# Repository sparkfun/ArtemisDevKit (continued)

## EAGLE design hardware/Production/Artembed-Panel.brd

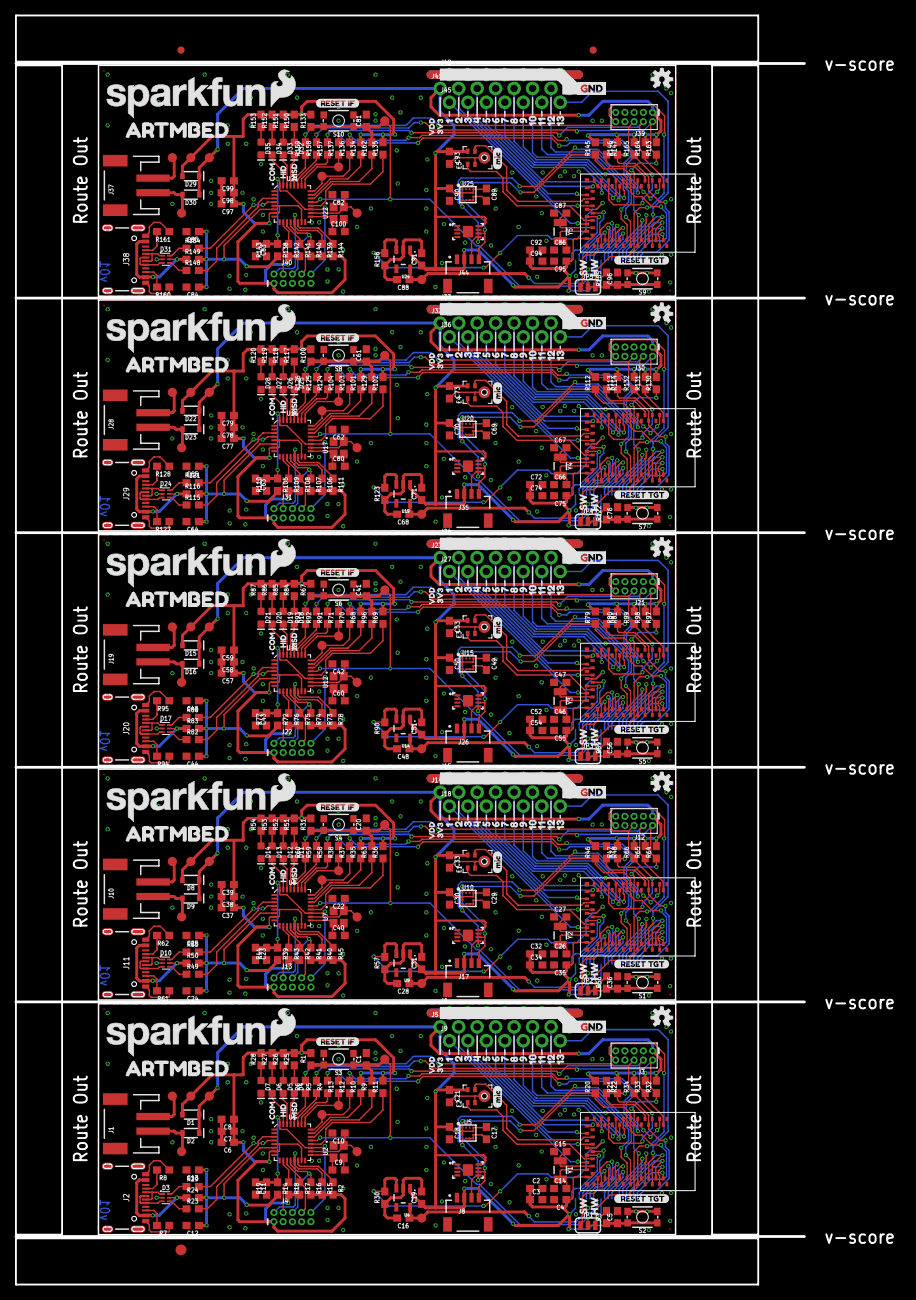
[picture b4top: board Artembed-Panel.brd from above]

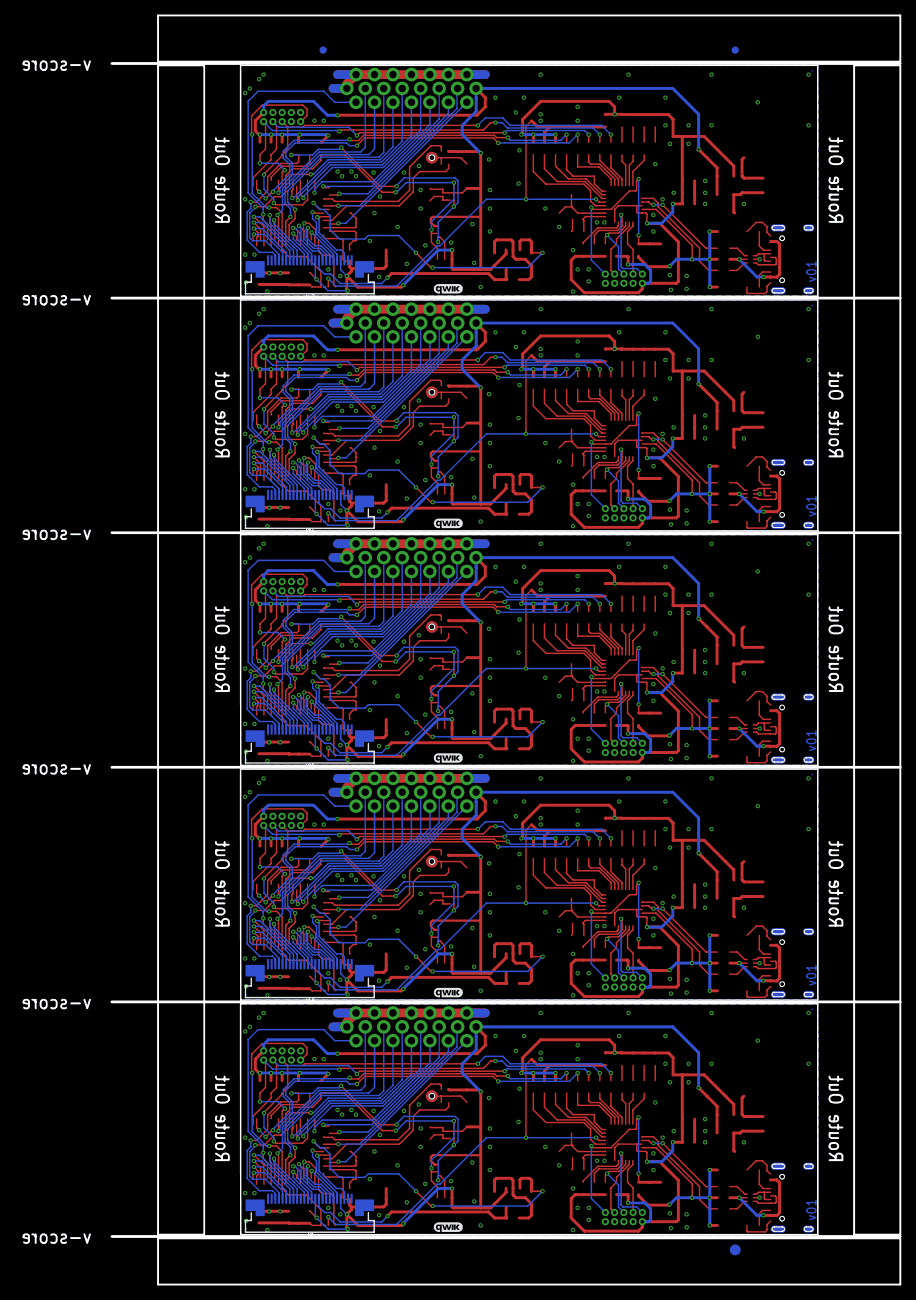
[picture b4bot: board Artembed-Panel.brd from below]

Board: 2 copper layers, 108.4 x 174.5 mm, 616 parts (23 on the bottom side), 405 nets.

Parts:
C1, C4, C7, C8, C11, C13, C17, C20, C23, C25, C29, C35, C38, C39, C41, C43, C45, C49, C55, C58, C59, C61, C63, C65, C69, C75, C78, C79, C81, C83, C85, C89, C95, C98, C99: 0.1uF; 0603
C2, C18, C30, C32, C50, C52, C70, C72, C90, C92: 10uF; 0603
C3, C12, C16, C19, C21, C24, C28, C31, C33, C34, C44, C48, C51, C53, C54, C64, C68, C71, C73, C74, C84, C88, C91, C93, C94: 1.0uF; 0603
C5, C36, C56, C76, C96: 1nF; 0603
C6, C37, C57, C77, C97: 2.2uF; 0603
C9, C10, C22, C40, C42, C60, C62, C80, C82, C100: 12pF; 0603
C14, C15, C26, C27, C46, C47, C66, C67, C86, C87: 15pF; 0603
D1, D2, D8, D9, D15, D16, D22, D23, D29, D30: 3A/10V/280mV; SOD-323
D3, D10, D17, D24, D31: PRTR5V0U2F; SOT886
D4, D11, D18, D25, D32: BLUE; LED-0603
D5, D12, D19, D26, D33: GREEN; LED-0603
D6, D13, D20, D27, D34: Yellow; LED-0603
D7, D14, D21, D28, D35: RED; LED-0603
E1, E2, E3, E4, E5: SPH0641LM4H-1; SPH0641LM4H-1_MICROPHONE
E$1, E$2, E$3, E$4: FIDUCIAL-1X2
E$5, E$6: FIDUCIAL-1.5X3
ECC1, ECC2, ECC3, ECC4, ECC5: ATECC508AUDFN_2X3MM; UDFN_2X3MM
FD1, FD2, FD3, FD4, FD5, FD6, FD7, FD8, FD9, FD10, FD11, FD12, FD13, FD14, FD15, FD16, FD17, FD18, FD19, FD20: FIDUCIAL0.2MM; FIDUCIAL-0.2MM
J1, J10, J19, J28, J37: JST-2-SMD
J2, J11, J20, J29, J38: USB-C-16P
J3, J12, J21, J30, J39: CORTEX_JTAG_DEBUG_MINIMUM_PTH; 2X5-PTH-1.27MM
J4, J13, J22, J31, J40: CORTEX_JTAG_DEBUG_PTH_NS; 2X5-PTH-1.27MM-NO_SILK
J5, J14, J23, J32, J41: 1X08_NO_SILK
J6, J9, J15, J18, J24, J27, J33, J36, J42, J45: 1X07_NO_SILK
J7, J16, J25, J34, J43: CAMERA-HIMAX; FPC-24-AMPHENOL-SFV24R-1STE1HLF
J8, J17, J26, J35, J44: JST04_1MM_RA
JP1, JP2, JP3, JP4, JP5: HW/SW RESET; SMT-JUMPER_3_1-NC_TRACE_SILK
LOGO1, LOGO3, LOGO5, LOGO7, LOGO9: OSHW-LOGOS; OSHW-LOGO-S
LOGO2, LOGO4, LOGO6, LOGO8, LOGO10: SFE_LOGO_NAME.2_INCH; SFE_LOGO_NAME_.2
R1, R2, R3, R19, R22, R30, R31, R44, R45, R48, R56, R57, R67, R77, R78, R81, R89, R90, R100, R110, R111, R114, R122, R123, R133, R143, R144, R147, R155, R156: 10k; 0603
R4, R5, R6, R9, R12, R13, R37, R38, R58, R59, R60, R63, R70, R71, R91, R92, R93, R96, R103, R104, R124, R125, R126, R129, R136, R137, R157, R158, R159, R162: 0; 0603
R7, R8, R61, R62, R94, R95, R127, R128, R160, R161: 5.1k; 0603
R10, R11, R15, R16, R17, R18, R32, R33, R34, R35, R36, R40, R41, R42, R43, R64, R65, R66, R68, R69, R73, R74, R75, R76, R97, R98, R99, R101, R102, R106, R107, R108, R109, R130, R131, R132, R134, R135, R139, R140, R141, R142, R163, R164, R165: DNP; 0603
R14, R39, R72, R105, R138: 5.62k; 0603
R20, R21, R46, R47, R79, R80, R112, R113, R145, R146: 2.2k; 0603
R23, R29, R49, R55, R82, R88, R115, R121, R148, R154: 33; 0603
R24, R50, R83, R116, R149: 10; 0603
R25, R26, R27, R28, R51, R52, R53, R54, R84, R85, R86, R87, R117, R118, R119, R120, R150, R151, R152, R153: 330; 0603
S1, S2, S5, S7, S9: RESET TGT; TACTILE_SWITCH_SMD_4.6X2.8MM
S3, S4, S6, S8, S10: RESET IF; TACTILE_SWITCH_SMD_4.6X2.8MM
TP1, TP2, TP19, TP28, TP37: TEST-POINT3X5; PAD.03X.05
TP3, TP4, TP5, TP6, TP7, TP8, TP9, TP10, TP11, TP12, TP13, TP14, TP15, TP16, TP17, TP18, TP20, TP21, TP22, TP23, TP24, TP25, TP26, TP27, TP29, TP30, TP31, TP32, TP33, TP34, TP35, TP36, TP38, TP39, TP40, TP41, TP42, TP43, TP44, TP45: PAD.03X.05
U1, U6, U11, U16, U21: DAPLINK_KL26Z; QFN-32-NOPAD
U2, U7, U12, U17, U22: 16MHz; CRYSTAL-SMD-2X2.5MM
U3, U8, U13, U18, U23: ARTEMIS_MODULESMD; ARTEMIS_FP
U4, U9, U14, U19, U24: 1.8V; SOT23-5
U5, U10, U15, U20, U25: LIS2DH12; LGA-12-LISDH12
U$1, U$15, U$55, U$82, U$109: 10
U$2, U$29, U$56, U$83, U$110: 21
U$3, U$30, U$57, U$84, U$111: 32
U$4, U$31, U$58, U$85, U$112: 43
U$5, U$32, U$59, U$86, U$113: 54
U$6, U$33, U$60, U$87, U$114: 65
U$7, U$34, U$61, U$88, U$115: 76
U$8, U$35, U$62, U$89, U$116: 87
U$9, U$36, U$63, U$90, U$117: 98
U$10, U$37, U$64, U$91, U$118: 109
U$11, U$38, U$65, U$92, U$119: 1110
U$12, U$39, U$66, U$93, U$120: 1211
U$13, U$40, U$67, U$94, U$121: 1312
U$14, U$41, U$68, U$95, U$122: GND13
U$16, U$42, U$69, U$96, U$123: SFE_LOGO_FLAME_.2
U$17, U$43, U$70, U$97, U$124: ARTMBED17
U$18, U$44, U$71, U$98, U$125: QWIIC_4MM
U$19, U$45, U$72, U$99, U$126: COM7
U$20, U$46, U$73, U$100, U$127: HID5
U$21, U$47, U$74, U$101, U$128: MSD6
U$22, U$48, U$75, U$102, U$129: MIC0
U$23, U$49, U$76, U$103, U$130: HW3
U$24, U$50, U$77, U$104, U$131: SW4
U$25, U$51, U$78, U$105, U$132: _RESET_TGT2
U$26, U$52, U$79, U$106, U$133: RESET_IF1
U$27, U$53, U$80, U$107, U$134: 3V39
U$28, U$54, U$81, U$108, U$135: VDD8
Y1, Y2, Y3, Y4, Y5: 32.768kHz; CRYSTAL-SMD-3.2X1.5MM

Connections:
1.8V: C16.1, J7.10, TP1.P$1, U4.5
1.8V1: C28.1, J16.10, TP2.P$1, U9.5
1.8V2: C48.1, J25.10, TP19.P$1, U14.5
1.8V3: C68.1, J34.10, TP28.P$1, U19.5
1.8V4: C88.1, J43.10, TP37.P$1, U24.5
3.3V: C6.1, C7.1, C8.1, D1.A, J4.1, R1.2, R2.2, R10.2, R11.2, R15.2, R16.2, R17.2, R18.2, R25.2, R26.2, R27.2, R28.2, TP13.P$1, U1.5, U1.7, U1.15
3.3V1: C37.1, C38.1, C39.1, D8.A, J13.1, R31.2, R35.2, R36.2, R40.2, R41.2, R42.2, R43.2, R45.2, R51.2, R52.2, R53.2, R54.2, TP14.P$1, U6.5, U6.7, U6.15
3.3V2: C57.1, C58.1, C59.1, D15.A, J22.1, R67.2, R68.2, R69.2, R73.2, R74.2, R75.2, R76.2, R78.2, R84.2, R85.2, R86.2, R87.2, TP23.P$1, U11.5, U11.7, U11.15
3.3V3: C77.1, C78.1, C79.1, D22.A, J31.1, R100.2, R101.2, R102.2, R106.2, R107.2, R108.2, R109.2, R111.2, R117.2, R118.2, R119.2, R120.2, TP32.P$1, U16.5, U16.7, U16.15
3.3V4: C97.1, C98.1, C99.1, D29.A, J40.1, R133.2, R134.2, R135.2, R139.2, R140.2, R141.2, R142.2, R144.2, R150.2, R151.2, R152.2, R153.2, TP41.P$1, U21.5, U21.7, U21.15
!RST: C11.1, J4.10, R14.1, R19.2, U1.19, U1.32
!RST1: C23.1, J13.10, R39.1, R44.2, U6.19, U6.32
!RST2: C43.1, J22.10, R72.1, R77.2, U11.19, U11.32
!RST3: C63.1, J31.10, R105.1, R110.2, U16.19, U16.32
!RST4: C83.1, J40.10, R138.1, R143.2, U21.19, U21.32
!TGT_RST: C1.1, JP1.2, R1.1, R9.2, S3.3, S3.4, TP11.P$1, U1.21
!TGT_RST1: C20.1, JP2.2, R31.1, R63.2, S4.3, S4.4, TP7.P$1, U6.21
!TGT_RST2: C41.1, JP3.2, R67.1, R96.2, S6.3, S6.4, TP21.P$1, U11.21
!TGT_RST3: C61.1, JP4.2, R100.1, R129.2, S8.3, S8.4, TP30.P$1, U16.21
!TGT_RST4: C81.1, JP5.2, R133.1, R162.2, S10.3, S10.4, TP39.P$1, U21.21
!TGT_RST!_HW: C5.1, J3.10, JP1.3, R3.1, S2.3, S2.4, U3.~RST
!TGT_RST!_HW1: C36.1, J12.10, JP2.3, R56.1, S1.3, S1.4, U8.~RST
!TGT_RST!_HW2: C56.1, J21.10, JP3.3, R89.1, S5.3, S5.4, U13.~RST
!TGT_RST!_HW3: C76.1, J30.10, JP4.3, R122.1, S7.3, S7.4, U18.~RST
!TGT_RST!_HW4: C96.1, J39.10, JP5.3, R155.1, S9.3, S9.4, U23.~RST
!TGT_RST!_SW: JP1.1, U3.~D19
!TGT_RST!_SW1: JP2.1, U8.~D19
!TGT_RST!_SW2: JP3.1, U13.~D19
!TGT_RST!_SW3: JP4.1, U18.~D19
!TGT_RST!_SW4: JP5.1, U23.~D19
CAMERA_D0: J7.14, U3.~D43
CAMERA_D1: J7.3, U3.AD34
CAMERA_D2: J7.9, U3.~AD31
CAMERA_D3: J7.5, U3.~AD33/SWO
CAMERA_D4: J7.12, U3.D41
CAMERA_D5: J7.20, U3.~D44
CAMERA_D6: J7.19, U3.~D37
CAMERA_D7: J7.13, U3.~D45
CAMERA_D8: J16.3, U8.AD34
CAMERA_D9: J16.5, U8.~AD33/SWO
CAMERA_D10: J16.12, U8.D41
CAMERA_D11: J16.20, U8.~D44
CAMERA_D12: J16.19, U8.~D37
CAMERA_D13: J16.13, U8.~D45
CAMERA_D14: J16.14, U8.~D43
CAMERA_D15: J16.9, U8.~AD31
CAMERA_D16: J25.3, U13.AD34
CAMERA_D17: J25.5, U13.~AD33/SWO
CAMERA_D18: J25.12, U13.D41
CAMERA_D19: J25.20, U13.~D44
CAMERA_D20: J25.19, U13.~D37
CAMERA_D21: J25.13, U13.~D45
CAMERA_D22: J25.14, U13.~D43
CAMERA_D23: J25.9, U13.~AD31
CAMERA_D24: J34.3, U18.AD34
CAMERA_D25: J34.5, U18.~AD33/SWO
CAMERA_D26: J34.12, U18.D41
CAMERA_D27: J34.20, U18.~D44
CAMERA_D28: J34.19, U18.~D37
CAMERA_D29: J34.13, U18.~D45
CAMERA_D30: J34.14, U18.~D43
CAMERA_D31: J34.9, U18.~AD31
CAMERA_D32: J43.3, U23.AD34
CAMERA_D33: J43.5, U23.~AD33/SWO
CAMERA_D34: J43.12, U23.D41
CAMERA_D35: J43.20, U23.~D44
CAMERA_D36: J43.19, U23.~D37
CAMERA_D37: J43.13, U23.~D45
CAMERA_D38: J43.14, U23.~D43
CAMERA_D39: J43.9, U23.~AD31
CAMERA_DVDD_EN: R30.2, U3.D15, U4.3
CAMERA_DVDD_EN1: R57.2, U8.D15, U9.3
CAMERA_DVDD_EN2: R90.2, U13.D15, U14.3
CAMERA_DVDD_EN3: R123.2, U18.D15, U19.3
CAMERA_DVDD_EN4: R156.2, U23.D15, U24.3
CAMERA_HSYNC: J7.16, U3.~D42
CAMERA_HSYNC1: J16.16, U8.~D42
CAMERA_HSYNC2: J25.16, U13.~D42
CAMERA_HSYNC3: J34.16, U18.~D42
CAMERA_HSYNC4: J43.16, U23.~D42
CAMERA_INT: J7.18, U3.D38
CAMERA_INT1: J16.18, U8.D38
CAMERA_INT2: J25.18, U13.D38
CAMERA_INT3: J34.18, U18.D38
CAMERA_INT4: J43.18, U23.D38
CAMERA_MCLK: J7.8, U3.~D18
CAMERA_MCLK1: J16.8, U8.~D18
CAMERA_MCLK2: J25.8, U13.~D18
CAMERA_MCLK3: J34.8, U18.~D18
CAMERA_MCLK4: J43.8, U23.~D18
CAMERA_PCLK: J7.17, U3.D36
CAMERA_PCLK1: J16.17, U8.D36
CAMERA_PCLK2: J25.17, U13.D36
CAMERA_PCLK3: J34.17, U18.D36
CAMERA_PCLK4: J43.17, U23.D36
CAMERA_TRIG: J7.7, U3.D17
CAMERA_TRIG1: J16.7, U8.D17
CAMERA_TRIG2: J25.7, U13.D17
CAMERA_TRIG3: J34.7, U18.D17
CAMERA_TRIG4: J43.7, U23.D17
CAMERA_VSYNC: J7.6, U3.AD16
CAMERA_VSYNC1: J16.6, U8.AD16
CAMERA_VSYNC2: J25.6, U13.AD16
CAMERA_VSYNC3: J34.6, U18.AD16
CAMERA_VSYNC4: J43.6, U23.AD16
D1: J9.1, U3.~AD29
D2: J5.2, U3.~AD13
D3: J9.2, U3.~D25
D4: J5.3, U3.~D6
D5: J9.3, U3.~D27
D6: J5.4, U3.~D4
D7: J9.4, U3.~AD35
D8: J5.5, U3.D7
D9: J9.5, U3.~D5
D10: J5.6, U3.D2
D11: J9.6, U3.D1
D12: J5.7, U3.D0
D13: J9.7, U3.D3
D14: J18.7, U8.D3
D15: J18.1, U8.~AD29
D16: J14.2, U8.~AD13
D17: J18.2, U8.~D25
D18: J14.3, U8.~D6
D19: J18.3, U8.~D27
D20: J14.4, U8.~D4
D21: J18.4, U8.~AD35
D22: J14.5, U8.D7
D23: J18.5, U8.~D5
D24: J14.6, U8.D2
D25: J18.6, U8.D1
D26: J14.7, U8.D0
D27: J27.7, U13.D3
D28: J27.1, U13.~AD29
D29: J23.2, U13.~AD13
D30: J27.2, U13.~D25
D31: J23.3, U13.~D6
D32: J27.3, U13.~D27
D33: J23.4, U13.~D4
D34: J27.4, U13.~AD35
D35: J23.5, U13.D7
D36: J27.5, U13.~D5
D37: J23.6, U13.D2
D38: J27.6, U13.D1
D39: J23.7, U13.D0
D40: J36.7, U18.D3
D41: J36.1, U18.~AD29
D42: J32.2, U18.~AD13
D43: J36.2, U18.~D25
D44: J32.3, U18.~D6
D45: J36.3, U18.~D27
D46: J32.4, U18.~D4
D47: J36.4, U18.~AD35
D48: J32.5, U18.D7
D49: J36.5, U18.~D5
D50: J32.6, U18.D2
D51: J36.6, U18.D1
D52: J32.7, U18.D0
D53: J45.7, U23.D3
D54: J45.1, U23.~AD29
D55: J41.2, U23.~AD13
D56: J45.2, U23.~D25
D57: J41.3, U23.~D6
D58: J45.3, U23.~D27
D59: J41.4, U23.~D4
D60: J45.4, U23.~AD35
D61: J41.5, U23.D7
D62: J45.5, U23.~D5
D63: J41.6, U23.D2
D64: J45.6, U23.D1
D65: J41.7, U23.D0
GND: C1.2, C2.2, C3.2, C4.2, C5.2, C6.2, C7.2, C8.2, C9.2, C10.2, C11.2, C12.2, C13.2, C14.1, C15.1, C16.2, C17.2, C18.2, C19.2, C21.2, D3.2, D7.C, E2.2, E2.3, E2.6, E2.7, E2.8, ECC1.4, ECC1.P, J1.2, J2.GND, J2.GND2, J3.3, J3.5, J3.9, J4.3, J4.5, J4.9, J5.8, J6.1, J6.2, J6.3, J6.4, J6.5, J6.6, J6.7, J7.2, J7.15, J8.1, R7.1, R8.1, R19.1, R22.1, R30.1, S2.1, S2.2, S3.1, S3.2, TP9.P$1, U1.2, U1.8, U1.16, U2.P2, U2.P4, U3.GND@1, U3.GND@22, U3.GND@38, U3.GND@39, U3.GND@47, U3.GND@59, U4.2, U5.5, U5.6, U5.7, U5.8
GND1: C20.2, C22.2, C23.2, C24.2, C25.2, C26.1, C27.1, C28.2, C29.2, C30.2, C31.2, C32.2, C33.2, C34.2, C35.2, C36.2, C37.2, C38.2, C39.2, C40.2, D10.2, D14.C, E1.2, E1.3, E1.6, E1.7, E1.8, ECC2.4, ECC2.P, J10.2, J11.GND, J11.GND2, J12.3, J12.5, J12.9, J13.3, J13.5, J13.9, J14.8, J15.1, J15.2, J15.3, J15.4, J15.5, J15.6, J15.7, J16.2, J16.15, J17.1, R44.1, R48.1, R57.1, R61.1, R62.1, S1.1, S1.2, S4.1, S4.2, TP18.P$1, U6.2, U6.8, U6.16, U7.P2, U7.P4, U8.GND@1, U8.GND@22, U8.GND@38, U8.GND@39, U8.GND@47, U8.GND@59, U9.2, U10.5, U10.6, U10.7, U10.8
GND2: C41.2, C42.2, C43.2, C44.2, C45.2, C46.1, C47.1, C48.2, C49.2, C50.2, C51.2, C52.2, C53.2, C54.2, C55.2, C56.2, C57.2, C58.2, C59.2, C60.2, D17.2, D21.C, E3.2, E3.3, E3.6, E3.7, E3.8, ECC3.4, ECC3.P, J19.2, J20.GND, J20.GND2, J21.3, J21.5, J21.9, J22.3, J22.5, J22.9, J23.8, J24.1, J24.2, J24.3, J24.4, J24.5, J24.6, J24.7, J25.2, J25.15, J26.1, R77.1, R81.1, R90.1, R94.1, R95.1, S5.1, S5.2, S6.1, S6.2, TP27.P$1, U11.2, U11.8, U11.16, U12.P2, U12.P4, U13.GND@1, U13.GND@22, U13.GND@38, U13.GND@39, U13.GND@47, U13.GND@59, U14.2, U15.5, U15.6, U15.7, U15.8
GND3: C61.2, C62.2, C63.2, C64.2, C65.2, C66.1, C67.1, C68.2, C69.2, C70.2, C71.2, C72.2, C73.2, C74.2, C75.2, C76.2, C77.2, C78.2, C79.2, C80.2, D24.2, D28.C, E4.2, E4.3, E4.6, E4.7, E4.8, ECC4.4, ECC4.P, J28.2, J29.GND, J29.GND2, J30.3, J30.5, J30.9, J31.3, J31.5, J31.9, J32.8, J33.1, J33.2, J33.3, J33.4, J33.5, J33.6, J33.7, J34.2, J34.15, J35.1, R110.1, R114.1, R123.1, R127.1, R128.1, S7.1, S7.2, S8.1, S8.2, TP36.P$1, U16.2, U16.8, U16.16, U17.P2, U17.P4, U18.GND@1, U18.GND@22, U18.GND@38, U18.GND@39, U18.GND@47, U18.GND@59, U19.2, U20.5, U20.6, U20.7, U20.8
GND4: C81.2, C82.2, C83.2, C84.2, C85.2, C86.1, C87.1, C88.2, C89.2, C90.2, C91.2, C92.2, C93.2, C94.2, C95.2, C96.2, C97.2, C98.2, C99.2, C100.2, D31.2, D35.C, E5.2, E5.3, E5.6, E5.7, E5.8, ECC5.4, ECC5.P, J37.2, J38.GND, J38.GND2, J39.3, J39.5, J39.9, J40.3, J40.5, J40.9, J41.8, J42.1, J42.2, J42.3, J42.4, J42.5, J42.6, J42.7, J43.2, J43.15, J44.1, R143.1, R147.1, R156.1, R160.1, R161.1, S9.1, S9.2, S10.1, S10.2, TP45.P$1, U21.2, U21.8, U21.16, U22.P2, U22.P4, U23.GND@1, U23.GND@22, U23.GND@38, U23.GND@39, U23.GND@47, U23.GND@59, U24.2, U25.5, U25.6, U25.7, U25.8
LED_HID: D5.C, U1.30
LED_HID1: D12.C, U6.30
LED_HID2: D19.C, U11.30
LED_HID3: D26.C, U16.30
LED_HID4: D33.C, U21.30
LED_MSD: D4.C, U1.29
LED_MSD1: D11.C, U6.29
LED_MSD2: D18.C, U11.29
LED_MSD3: D25.C, U16.29
LED_MSD4: D32.C, U21.29
LED_UART: D6.C, U1.31
LED_UART1: D13.C, U6.31
LED_UART2: D20.C, U11.31
LED_UART3: D27.C, U16.31
LED_UART4: D34.C, U21.31
unnamed: D4.A, R25.1
unnamed: D5.A, R26.1
unnamed: D6.A, R27.1
unnamed: J2.B5, R7.2
unnamed: J2.A5, R8.2
unnamed: D11.A, R51.1
unnamed: D7.A, R28.1
unnamed: D3.4, R23.1
unnamed: D3.6, R29.1
unnamed: R2.1, U1.14
unnamed: R11.1, U1.20
unnamed: D12.A, R52.1
unnamed: C9.1, U1.17, U2.P1
unnamed: C14.2, U3.XI, Y1.P$2
unnamed: C15.2, U3.XO, Y1.P$1
unnamed: C10.1, TP5.P$1, U1.18, U2.P3
unnamed: R12.1, TP3.P$1, U1.24
unnamed: R13.1, TP4.P$1, U1.25
unnamed: R10.1, U1.23
unnamed: R22.2, U3.BOOT
unnamed: D2.A, J1.1, TP12.P$1
unnamed: R9.1, U1.22
unnamed: R4.1, U1.26
unnamed: R5.1, U1.27
unnamed: R6.1, U1.28
unnamed: D13.A, R53.1
unnamed: J11.B5, R61.2
unnamed: J11.A5, R62.2
unnamed: D10.4, R49.1
unnamed: D10.6, R55.1
unnamed: D14.A, R54.1
unnamed: R45.1, U6.14
unnamed: C40.1, U6.17, U7.P1
unnamed: C22.1, TP17.P$1, U6.18, U7.P3
unnamed: R36.1, U6.20
unnamed: R35.1, U6.23
unnamed: D9.A, J10.1, TP8.P$1
unnamed: R63.1, U6.22
unnamed: R58.1, U6.26
unnamed: R59.1, U6.27
unnamed: R60.1, U6.28
unnamed: C26.2, U8.XI, Y2.P$2
unnamed: C27.2, U8.XO, Y2.P$1
unnamed: R37.1, TP15.P$1, U6.24
unnamed: R38.1, TP16.P$1, U6.25
unnamed: R48.2, U8.BOOT
unnamed: D18.A, R84.1
unnamed: D19.A, R85.1
unnamed: D20.A, R86.1
unnamed: J20.B5, R94.2
unnamed: J20.A5, R95.2
unnamed: D17.4, R82.1
unnamed: D17.6, R88.1
unnamed: D21.A, R87.1
unnamed: R78.1, U11.14
unnamed: C60.1, U11.17, U12.P1
unnamed: C42.1, TP26.P$1, U11.18, U12.P3
unnamed: R69.1, U11.20
unnamed: R68.1, U11.23
unnamed: D16.A, J19.1, TP22.P$1
unnamed: R96.1, U11.22
unnamed: R91.1, U11.26
unnamed: R92.1, U11.27
unnamed: R93.1, U11.28
unnamed: C46.2, U13.XI, Y3.P$2
unnamed: C47.2, U13.XO, Y3.P$1
unnamed: R70.1, TP24.P$1, U11.24
unnamed: R71.1, TP25.P$1, U11.25
unnamed: R81.2, U13.BOOT
unnamed: D25.A, R117.1
unnamed: D26.A, R118.1
unnamed: D27.A, R119.1
unnamed: J29.B5, R127.2
unnamed: J29.A5, R128.2
unnamed: D24.4, R115.1
unnamed: D24.6, R121.1
unnamed: D28.A, R120.1
unnamed: R111.1, U16.14
unnamed: C80.1, U16.17, U17.P1
unnamed: C62.1, TP35.P$1, U16.18, U17.P3
unnamed: R102.1, U16.20
unnamed: R101.1, U16.23
unnamed: D23.A, J28.1, TP31.P$1
unnamed: R129.1, U16.22
unnamed: R124.1, U16.26
unnamed: R125.1, U16.27
unnamed: R126.1, U16.28
unnamed: C66.2, U18.XI, Y4.P$2
unnamed: C67.2, U18.XO, Y4.P$1
unnamed: R103.1, TP33.P$1, U16.24
unnamed: R104.1, TP34.P$1, U16.25
unnamed: R114.2, U18.BOOT
unnamed: D32.A, R150.1
unnamed: D33.A, R151.1
unnamed: D34.A, R152.1
unnamed: J38.B5, R160.2
unnamed: J38.A5, R161.2
unnamed: D31.4, R148.1
unnamed: D31.6, R154.1
unnamed: D35.A, R153.1
unnamed: R144.1, U21.14
unnamed: C100.1, U21.17, U22.P1
unnamed: C82.1, TP44.P$1, U21.18, U22.P3
unnamed: R135.1, U21.20
unnamed: R134.1, U21.23
unnamed: D30.A, J37.1, TP40.P$1
unnamed: R162.1, U21.22
unnamed: R157.1, U21.26
unnamed: R158.1, U21.27
unnamed: R159.1, U21.28
unnamed: C86.2, U23.XI, Y5.P$2
unnamed: C87.2, U23.XO, Y5.P$1
unnamed: R136.1, TP42.P$1, U21.24
unnamed: R137.1, TP43.P$1, U21.25
unnamed: R147.2, U23.BOOT
PDM_CLK: E2.4, U3.~AD12
PDM_CLK1: E1.4, U8.~AD12
PDM_CLK2: E3.4, U13.~AD12
PDM_CLK3: E4.4, U18.~AD12
PDM_CLK4: E5.4, U23.~AD12
PDM_DATA: E2.1, U3.~AD11
PDM_DATA1: E1.1, U8.~AD11
PDM_DATA2: E3.1, U13.~AD11
PDM_DATA3: E4.1, U18.~AD11
PDM_DATA4: E5.1, U23.~AD11
SCL: ECC1.6, J7.21, J8.4, R20.1, U3.D8, U5.1
SCL1: ECC2.6, J16.21, J17.4, R46.1, U8.D8, U10.1
SCL2: ECC3.6, J25.21, J26.4, R79.1, U13.D8, U15.1
SCL3: ECC4.6, J34.21, J35.4, R112.1, U18.D8, U20.1
SCL4: ECC5.6, J43.21, J44.4, R145.1, U23.D8, U25.1
SDA: ECC1.5, J7.22, J8.3, R21.1, U3.D9, U5.4
SDA1: ECC2.5, J16.22, J17.3, R47.1, U8.D9, U10.4
SDA2: ECC3.5, J25.22, J26.3, R80.1, U13.D9, U15.4
SDA3: ECC4.5, J34.22, J35.3, R113.1, U18.D9, U20.4
SDA4: ECC5.5, J43.22, J44.3, R146.1, U23.D9, U25.4
TCLK: J4.4, R18.1, U1.10
TCLK1: J13.4, R43.1, U6.10
TCLK2: J22.4, R76.1, U11.10
TCLK3: J31.4, R109.1, U16.10
TCLK4: J40.4, R142.1, U21.10
TDI: J4.8, R17.1, U1.11
TDI1: J13.8, R42.1, U6.11
TDI2: J22.8, R75.1, U11.11
TDI3: J31.8, R108.1, U16.11
TDI4: J40.8, R141.1, U21.11
TDO: J4.6, R16.1, U1.12
TDO1: J13.6, R41.1, U6.12
TDO2: J22.6, R74.1, U11.12
TDO3: J31.6, R107.1, U16.12
TDO4: J40.6, R140.1, U21.12
TGT_RX: R13.2, U3.TXO-0
TGT_RX1: R38.2, U8.TXO-0
TGT_RX2: R71.2, U13.TXO-0
TGT_RX3: R104.2, U18.TXO-0
TGT_RX4: R137.2, U23.TXO-0
TGT_SWCLK: J3.4, R4.2, R33.1, U3.SWDCK
TGT_SWCLK1: J12.4, R58.2, R65.1, U8.SWDCK
TGT_SWCLK2: J21.4, R91.2, R98.1, U13.SWDCK
TGT_SWCLK3: J30.4, R124.2, R131.1, U18.SWDCK
TGT_SWCLK4: J39.4, R157.2, R164.1, U23.SWDCK
TGT_SWDIO: J3.2, R5.2, R32.1, U3.SWDIO
TGT_SWDIO1: J12.2, R59.2, R64.1, U8.SWDIO
TGT_SWDIO2: J21.2, R92.2, R97.1, U13.SWDIO
TGT_SWDIO3: J30.2, R125.2, R130.1, U18.SWDIO
TGT_SWDIO4: J39.2, R158.2, R163.1, U23.SWDIO
TGT_SWO: J3.6, R6.2, R34.1, U3.~D22
TGT_SWO1: J12.6, R60.2, R66.1, U8.~D22
TGT_SWO2: J21.6, R93.2, R99.1, U13.~D22
TGT_SWO3: J30.6, R126.2, R132.1, U18.~D22
TGT_SWO4: J39.6, R159.2, R165.1, U23.~D22
TGT_TX: R12.2, U3.RXI-0
TGT_TX1: R37.2, U8.RXI-0
TGT_TX2: R70.2, U13.RXI-0
TGT_TX3: R103.2, U18.RXI-0
TGT_TX4: R136.2, U23.RXI-0
TMS: J4.2, R15.1, U1.13
TMS1: J13.2, R40.1, U6.13
TMS2: J22.2, R73.1, U11.13
TMS3: J31.2, R106.1, U16.13
TMS4: J40.2, R139.1, U21.13
USB_D+_P: R23.2, U1.3
USB_D+_P1: R49.2, U6.3
USB_D+_P2: R82.2, U11.3
USB_D+_P3: R115.2, U16.3
USB_D+_P4: R148.2, U21.3
USB_D+_R: D3.3, J2.A6, J2.B6
USB_D+_R1: D10.3, J11.A6, J11.B6
USB_D+_R2: D17.3, J20.A6, J20.B6
USB_D+_R3: D24.3, J29.A6, J29.B6
USB_D+_R4: D31.3, J38.A6, J38.B6
USB_D-_P: R29.2, U1.4
USB_D-_P1: R55.2, U6.4
USB_D-_P2: R88.2, U11.4
USB_D-_P3: R121.2, U16.4
USB_D-_P4: R154.2, U21.4
USB_D-_R: D3.1, J2.A7, J2.B7
USB_D-_R1: D10.1, J11.A7, J11.B7
USB_D-_R2: D17.1, J20.A7, J20.B7
USB_D-_R3: D24.1, J29.A7, J29.B7
USB_D-_R4: D31.1, J38.A7, J38.B7
VBUS_IF: D3.5, J2.VBUS1, J2.VBUS2, R24.1
VBUS_IF1: D10.5, J11.VBUS1, J11.VBUS2, R50.1
VBUS_IF2: C12.1, C13.1, R14.2, R24.2, U1.6
VBUS_IF3: C24.1, C25.1, R39.2, R50.2, U6.6
VBUS_IF4: D17.5, J20.VBUS1, J20.VBUS2, R83.1
VBUS_IF5: C44.1, C45.1, R72.2, R83.2, U11.6
VBUS_IF6: D24.5, J29.VBUS1, J29.VBUS2, R116.1
VBUS_IF7: C64.1, C65.1, R105.2, R116.2, U16.6
VBUS_IF8: D31.5, J38.VBUS1, J38.VBUS2, R149.1
VBUS_IF9: C84.1, C85.1, R138.2, R149.2, U21.6
VDD: C2.1, C3.1, C4.1, C17.1, C18.1, C19.1, C21.1, D1.C, D2.C, E2.5, ECC1.8, J3.1, J5.1, J7.4, J7.11, J8.2, R3.2, R20.2, R21.2, R32.2, R33.2, R34.2, TP10.P$1, U3.VDD@36, U3.VDD@37, U4.1, U5.2, U5.3, U5.9, U5.10
VDD1: C29.1, C30.1, C31.1, C32.1, C33.1, C34.1, C35.1, D8.C, D9.C, E1.5, ECC2.8, J12.1, J14.1, J16.4, J16.11, J17.2, R46.2, R47.2, R56.2, R64.2, R65.2, R66.2, TP6.P$1, U8.VDD@36, U8.VDD@37, U9.1, U10.2, U10.3, U10.9, U10.10
VDD2: C49.1, C50.1, C51.1, C52.1, C53.1, C54.1, C55.1, D15.C, D16.C, E3.5, ECC3.8, J21.1, J23.1, J25.4, J25.11, J26.2, R79.2, R80.2, R89.2, R97.2, R98.2, R99.2, TP20.P$1, U13.VDD@36, U13.VDD@37, U14.1, U15.2, U15.3, U15.9, U15.10
VDD3: C69.1, C70.1, C71.1, C72.1, C73.1, C74.1, C75.1, D22.C, D23.C, E4.5, ECC4.8, J30.1, J32.1, J34.4, J34.11, J35.2, R112.2, R113.2, R122.2, R130.2, R131.2, R132.2, TP29.P$1, U18.VDD@36, U18.VDD@37, U19.1, U20.2, U20.3, U20.9, U20.10
VDD4: C89.1, C90.1, C91.1, C92.1, C93.1, C94.1, C95.1, D29.C, D30.C, E5.5, ECC5.8, J39.1, J41.1, J43.4, J43.11, J44.2, R145.2, R146.2, R155.2, R163.2, R164.2, R165.2, TP38.P$1, U23.VDD@36, U23.VDD@37, U24.1, U25.2, U25.3, U25.9, U25.10

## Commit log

2019-09-13 progress commit
    got a lot of routing done, but more to do
2019-09-13 progress
2019-09-16 Back up small form factor
    Moving to a more prototyping friendly large form factor for now
2019-09-16 Remove board to start fresh
2019-09-17 Pre proto review
    Waiting on XTAL footprint update from Eli
2019-09-17 Update XTAL from Eli
2019-09-19 proto review revisions, panelized, cammed
2019-09-25 panelized + cammed
2019-10-09 add docs
2020-02-29 remove old stuff
2020-02-29 initial commit of v02 schematic
2020-03-02 work check 03/02
2020-03-03 checkpoint
2020-03-03 finished routing camera
2020-03-03 routed gpio
2020-03-03 ground purs and all airwires gone
2020-03-04 added top silkscreen
2020-03-04 add info silk, ran checklist
2020-03-04 generated v02 gerbers
2020-03-11 generate bom csv
2020-03-12 lay out labels for build sheet
2020-05-28 clean slate for v03
    - renamed to ArtemisDevKit
    - renamed parts library
    - removed old gerber files
    - removed old BOM
    - added .DS_Store to .gitignore for MacOS
2020-05-28 initial changes for v03
    - moved Apollo3 reset (TGT_RESET) to TARGET_NRESET on interface chip (pin c1)
    - moved TGT_BOOT to pin e30 (pad 9) of the interface chip (still meant to be pulled low most of the time - just making provisions for software control / serial bootloader compatibility later)
    - removed test point on clock lines
2020-05-28 board changes to match initial changes
2020-05-29 update labels
2020-06-01 connect PTB1 to PTC1
    PTB1 (pin 21 on the 32-pin QFN package) is for 'SW_RESET_BUTTON' in the DAPLink firmware - this is for detecting when the user wants to enter DAPLink maintenance mode
    PTC1 (pin 22 on the 32-pin package) is meant to actually control the reset line of the Artemis - this was the mistake that was fixed with a green-wire on the v02 prototype.
    The effect of this change is that the user can hold the Artemis reset line while plugging in the DK to enter maintenance mode where they can upgrade the interface firmware, and also that the Artemis 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
2020-06-01 remove unused connectors from special parts library
2020-06-01 final touches for review
    - updated library in use for the interface chip
    - mitered jumper labels
    - approved / fixed all drc errors
2020-06-01 rework TGT_RST routing
    just a minor optimization
2020-06-05 remove old buzzard libraries and delete old silk
2020-06-05 vector font in .sch
2020-06-05 add buzzard submodule
2020-06-05 initial addition of buzzard labels
2020-06-05 Update buzzard
2020-06-05 update buzzard labels
2020-06-05 apply changes from proto review
    - labeled jumpers w/ matching names and description
    - labeled accelerometer axes (bottom)
    - increaded power trace widths to 24 mil
    - removed VUSB current limiting resistor
    - increased buzzard label sizes
    - added AP2112K 3.3V regulator (disconnected MKL26Z regulator output from 3.3V bus to avoid contention)
2020-06-05 update to use MKL26Z128VFM4 from SparkFun library
2020-06-08 update eagle libraries in brd + sch
2020-06-08 replace sparkfun logo in schematic
2020-06-08 update eagle libs and add LED silk
2020-06-08 add overbar to reset label
2020-06-08 add checklist tools
2020-06-08 perform checklist for v03
2020-06-10 QC double check changes
2020-06-19 assembly sheet cleanup
2020-06-24 shift USB-C connector down 50 mil
    this is to make it properly centered on the board
    purely aesthetic motivation, with copper changes
2020-06-24 shift tgt swd connector
    this centers the label between the labels for the mic and acc
2020-06-24 Dimensions for board layout
    As of 6/24/20
2020-07-07 address Pete's reviews
    - improve GND pour on lower layer
    - fix ERC errors (mismatched values, footprints)
    - add LED buzzard labels
    - fix version in copper and schematic
2020-07-07 remove buzzard submodule
2020-07-07 replace buzzard with sparkX repo
2020-07-07 update silkscreen
2020-07-07 add test points for interface JTAG
2020-07-07 fix camera connector
2020-07-08 final design checklist
    -removed I2C PU resistors
    - switched bubble labels to UPPER CASE
    - ran checklist
2020-07-08 reorganize checklist
2020-07-08 remove VIN maximum
2020-07-10 panelize + CAM v10
2020-07-10 fix crooked frame on panel
2020-07-10 CAM for v10
2020-07-10 regenerate gerbers
    fixes crooked silk on the power output pins
2020-07-14 replace 8+4 smd headers with 12
2020-07-15 move an ugly trace
2020-07-15 approve drc errors
2020-07-15 generate gerbers
2020-08-17 Update ArtemisDevKit.brd
    Added measurements for components to dimensions layer
2020-08-17 Update ArtemisDevKit_dimensions.pdf
    Updated measurements
2020-09-11 Added support documentation
    Added the usual license, readme, contribution, and issue template documentation for a hardware repository
2020-09-11 Fix .json link
    Fix the way the `.json` file was linked/displayed
2020-10-14 Add graphical datasheet and func. block diagram
    Add graphical datasheet and board functional block diagram for Artemis DK
2020-10-14 Update repository content information
    File structure was incorrect
2020-10-14 Add Apollo3 chipset block diagram
    Add for Mbed documentation
